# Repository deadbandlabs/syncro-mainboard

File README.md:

# Deadband Labs Syncro

|||
| :---: | :---: |
|  |  |

A USB HID force-feedback interceptor between a PC and FFB devices, based on the
MYIR MYC-YF135 SOM (STM32MP135) and fully USB bus powered.

The board has three USB-A downstream ports, with a runtime-switched two-position topology mux:

- Mode 1 (default): the PC sees the SOM as a USB gadget; downstream
  ports sit behind the hub on the SOM host port.
- Mode 2: USB-C feeds the hub uplink and downstream ports connect to the PC
  directly, with the SOM as a peer device, for downstream device management.

The board also serves as an STM32MP13 development board, with Qwiic and
mikroBUS (unpopulated) as GPIO expansion, SWD, UART debug header, user buttons
and RGB status and accent LEDs.

## Hardware

- STM32MP13, 1GHz Cortex A7, 256MB DDR3L; boots from on-module 256MB SPI NAND,
  USB DFU on SW2, or SDMMC
- USB-C device port (fixed 5.1 kOhm Rd both CC pins, no PD or CC sensing)
- FE1.1s 4-port hub, three downstream ports on horizontal USB-A, each with
  common-mode filter + ESD (ECMF02-2AMX6)
- Input eFuse (647 mA) + reverse blocking on the 5 V rail
- microSD slot (SDMMC1), console UART on a 1x3 0.1" header, SWD on a
  1.27 mm 10-pin
- Qwiic (J9), mikroBUS/Click footprint (J8), reset/DFU/case-user buttons,
  RGB status LED on TIM1, three accent RGB LEDs on TIM8 (D16-D18)
- 4 layer, 1.6 mm, ENIG, JLC04161H-3313; single-sided SMT assembly

## Opening the design

Designed in KiCad 10. Open `syncro-mainboard/syncro-mainboard.kicad_pro` from a
clone of this repository. Libraries use paths relative to the project
(`${KIPRJMOD}/../syncro-pcb-lib/`), so no library setup is needed. Vendor
datasheets, vendor 3D models, fabrication outputs and internal DFT tools are not
included. _As a result, missing-3D-model warnings are expected._ This does not affect
the schematic, layout, DRC or plots.

Part numbers as assembled are in the LCSC fields on the schematic symbols.

## Interfaces

### Qwiic (J9)

JST SH 1.0 mm, 4 pin, horizontal: `GND`, `3V3`, `SDA` (`PF3`) and `SCL` (`PH13`),
both on I2C5 and shared with the mikroBUS socket, with 10 kOhm pull-ups fitted.
Qwiic modules usually also provide pull-ups, so a long chain may over-pull the bus.
Prefer a module without pull-ups or drop bus speed to 100 kHz.

### mikroBUS / Click (J8, DNP)

Standard mikroBUS pinout on two 1x8 sockets at 22.86 mm row spacing. All 12
IO signals route to SOM GPIO, chosen for the roles below:

| Pin | mikroBUS | Board net | SOM pad | SOM port | Roles |
|---:|---|---|---:|---|---|
| 1 | `AN` | `AIO1` | 48 | PA1 | ADC1/2_INP3, TIM2_CH2, TIM5_CH2, TIM15_CH1N |
| 2 | `RST` | `RST` | 92 | PA5 | ADC1_INP2, TIM2_CH1 |
| 3 | `CS` | `SPI_CS` | 80 | PA4 | SPI1, ADC1_INP14, ClickID 1-Wire |
| 4 | `SCK` | `SPI_SCK` | 79 | PC3 | SPI1, I2S1_CK, ADC1_INP13 |
| 5 | `MISO` | `SPI_MISO` | 77 | PA6 | SPI1, ADC1_INP17, TIM3_CH1, TIM13_CH1 |
| 6 | `MOSI` | `SPI_MOSI` | 78 | PA3 | SPI1, I2S1_SDO, ADC1_INP12 |
| 7 | `3V3` | `3V3` | 16 | - | keep under 100 mA, no limit |
| 8 | `GND` | `GND` | - | - | |
| 9 | `PWM` | `AIO0` | 47 | PA2 | ADC1/2_INP1, TIM2_CH3, TIM5_CH3, TIM15_CH1 |
| 10 | `INT` | `INT` | 91 | PF11 | ADC1/2_INP8 |
| 11 | `RX` | `CAN_RX` | 96 | PB5 | FDCAN2, UART5_RX, TIM3_CH2 |
| 12 | `TX` | `CAN_TX` | 95 | PB13 | FDCAN2, UART5_TX, LPTIM2_OUT |
| 13 | `SCL` | `I2C_SCL` | 133 | PH13 | I2C5 |
| 14 | `SDA` | `I2C_SDA` | 132 | PF3 | I2C5 |
| 15 | `5V` | `SYS_5V` | - | - | board 5 V rail |
| 16 | `GND` | `GND` | - | - | |

`AN` and `PWM` use a 330 Ohm series resistor, remaining GPIO 33 Ohm
for protection. All pins share two 0.3 pF ESD arrays. `RX`/`TX`
for UART5 also support FDCAN2 directly, so a CAN transceiver Click should work.

### Console (J2) and SWD (J3)

| J2 pin | Signal |
|---:|---|
| 1 | `GND` |
| 2 | `UART4_TX` |
| 3 | `UART4_RX` |

J3 is a standard ARM Cortex Debug 10-pin, 1.27 mm: pin 1 `VTref` on `VDD_3V3`,
SWDIO/SWCLK plus reset.

### USB

- J1 (USB-C): device port; reaches the SOM in mode 1, hub port 1 in mode 2.
- J5-J7 (USB-A): hub ports 2-4, shells to GND, sharing a VBUS current limit of
  about 250 mA (200-300 mA over tolerance) set by a TPS25200.

### microSD (J4)

SDMMC1 via an EMIF06-MSD02N16, which provides series resistance, filter
capacitance, ESD and card detect on SOM pad 110 (`PD12`). Normally empty, meant
for development or as an alternate boot target using a cut trace on the bottom
of the board.

### Power budget

USB-A's ~250 mA limit leaves about 400 mA for the SOM (measured 128 mA average,
~160 mA peak), the hub (30-80 mA) and everything else, inside the 647 mA nominal
input eFuse limit (590-710 mA over tolerance, 150 kOhm ILIM). A PC USB 2.0 port
generally only guarantees 500 mA, so downstream devices should be self-powered
for best reliability.

GPIO peripherals are powered from the SOM's 3V3 output, shared with the rest of
the board and with no limiting eFuse on these pins. Keep the total under 100 mA
to avoid brownout.

## Software

The board's OS (TF-A, OP-TEE, U-Boot, Linux kernel and rootfs) is built
with the Deadband Labs Buildroot SDK:
<https://github.com/deadbandlabs/dbl-buildroot>. It builds a complete image from
upstream sources that boots the MYIR SOM, with console, USB gadget and host,
SPI NAND and SD card enabled in the device tree.

dbl-buildroot is designed to be extended by a parent project: a device tree
include applied on top of the base tree, plus a `BR2_EXTERNAL` tree adding
packages, overlays and defconfigs, see its
[Parent Integration](https://github.com/deadbandlabs/dbl-buildroot/wiki/7.-Parent-Integration)
page. Carrier board peripherals (USB hub control, Qwiic and I2C, mikroBUS and so
on) are implemented this way. The Syncro userspace and its board layer are
pending final publication and will be linked here when complete.

## Licence

Design files: CERN-OHL-W-2.0, see `LICENSE` and `NOTICE`.

A design using the board only through its external interfaces (USB ports, Qwiic,
mikroBUS/Click, console serial header and SWD) is External Material under
section 1.8 of the licence and does not need to be released. Modified design
files must be published under the same licence.

`syncro-pcb-lib/` is generated from the project's parts library (see
`syncro-pcb-lib/GENERATED.md`), and part of it derives from stock KiCad libraries,
which stay CC-BY-SA-4.0 with the KiCad libraries exception. See `NOTICE`.

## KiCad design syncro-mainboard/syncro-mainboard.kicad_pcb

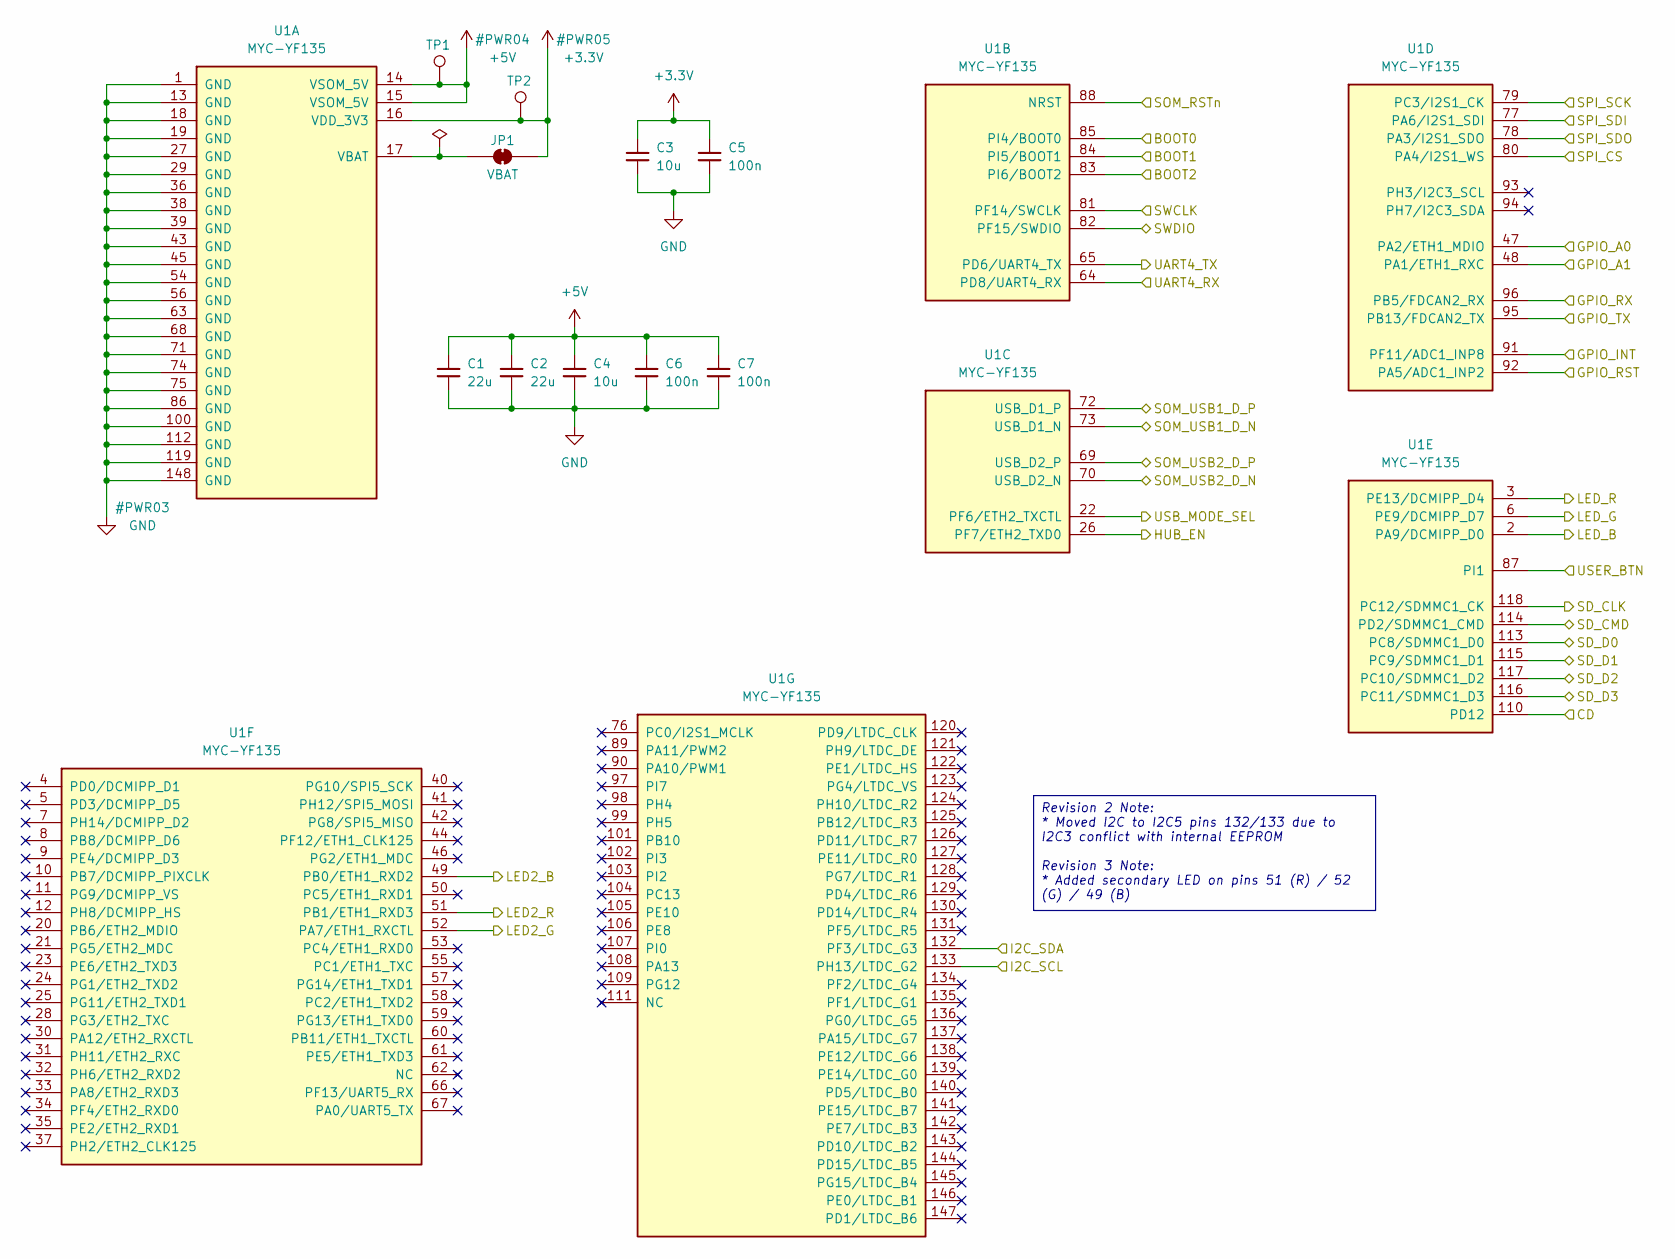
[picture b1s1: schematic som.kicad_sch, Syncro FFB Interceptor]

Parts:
C1, C2: 22u; C_0805_2012Metric; LCSC C45783
C3, C4: 10u; C_0805_2012Metric; LCSC C15850
C5, C6, C7: 100n; C_0402_1005Metric; LCSC C1525
JP1: VBAT; SolderJumper-2_P1.3mm_Bridged_RoundedPad1.0x1.5mm
TP1: 5V; TestPoint_Pad_D1.5mm
TP2: 3V3; TestPoint_Pad_D1.5mm
U1: MYC-YF135; MPN MYC-YF135F-256N256D-100-I

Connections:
+3.3V: C3.1, C5.1, JP1.2 (B), TP2.1 (1_1), U1.16 (VDD_3V3); also elsewhere on the board
+5V: C1.1, C2.1, C4.1, C6.1, C7.1, TP1.1 (1_1), U1.14 (VSOM_5V), U1.15 (VSOM_5V); also elsewhere on the board
/Debug/BOOT0: U1.85 (PI4/BOOT0); also elsewhere on the board
/Debug/BOOT1: U1.84 (PI5/BOOT1); also elsewhere on the board
/Debug/BOOT2: U1.83 (PI6/BOOT2); also elsewhere on the board
/Debug/SOM_RSTn: U1.88 (NRST); also elsewhere on the board
/Debug/SWCLK: U1.81 (PF14/SWCLK); also elsewhere on the board
/Debug/SWDIO: U1.82 (PF15/SWDIO); also elsewhere on the board
/Debug/UART4_RX: U1.64 (PD8/UART4_RX); also elsewhere on the board
/Debug/UART4_TX: U1.65 (PD6/UART4_TX); also elsewhere on the board
/STM32MP13 SOM/GPIO_A0: U1.47 (PA2/ETH1_MDIO); also elsewhere on the board
/STM32MP13 SOM/GPIO_A1: U1.48 (PA1/ETH1_RXC); also elsewhere on the board
/STM32MP13 SOM/GPIO_INT: U1.91 (PF11/ADC1_INP8); also elsewhere on the board
/STM32MP13 SOM/GPIO_RST: U1.92 (PA5/ADC1_INP2); also elsewhere on the board
/STM32MP13 SOM/GPIO_RX: U1.96 (PB5/FDCAN2_RX); also elsewhere on the board
/STM32MP13 SOM/GPIO_TX: U1.95 (PB13/FDCAN2_TX); also elsewhere on the board
/STM32MP13 SOM/HUB_EN: U1.26 (PF7/ETH2_TXD0); also elsewhere on the board
/STM32MP13 SOM/I2C_SCL: U1.133 (PH13/LTDC_G2); also elsewhere on the board
/STM32MP13 SOM/I2C_SDA: U1.132 (PF3/LTDC_G3); also elsewhere on the board
/STM32MP13 SOM/LED2_B: U1.49 (PB0/ETH1_RXD2); also elsewhere on the board
/STM32MP13 SOM/LED2_G: U1.52 (PA7/ETH1_RXCTL); also elsewhere on the board
/STM32MP13 SOM/LED2_R: U1.51 (PB1/ETH1_RXD3); also elsewhere on the board
/STM32MP13 SOM/LED_B: U1.2 (PA9/DCMIPP_D0); also elsewhere on the board
/STM32MP13 SOM/LED_G: U1.6 (PE9/DCMIPP_D7); also elsewhere on the board
/STM32MP13 SOM/LED_R: U1.3 (PE13/DCMIPP_D4); also elsewhere on the board
/STM32MP13 SOM/SD_CLK: U1.118 (PC12/SDMMC1_CK); also elsewhere on the board
/STM32MP13 SOM/SD_CMD: U1.114 (PD2/SDMMC1_CMD); also elsewhere on the board
/STM32MP13 SOM/SD_D0: U1.113 (PC8/SDMMC1_D0); also elsewhere on the board
/STM32MP13 SOM/SD_D1: U1.115 (PC9/SDMMC1_D1); also elsewhere on the board
/STM32MP13 SOM/SD_D2: U1.117 (PC10/SDMMC1_D2); also elsewhere on the board
/STM32MP13 SOM/SD_D3: U1.116 (PC11/SDMMC1_D3); also elsewhere on the board
/STM32MP13 SOM/SOM_USB1_D_N: U1.73 (USB_D1_N); also elsewhere on the board
/STM32MP13 SOM/SOM_USB1_D_P: U1.72 (USB_D1_P); also elsewhere on the board
/STM32MP13 SOM/SOM_USB2_D_N: U1.70 (USB_D2_N); also elsewhere on the board
/STM32MP13 SOM/SOM_USB2_D_P: U1.69 (USB_D2_P); also elsewhere on the board
/STM32MP13 SOM/SPI_CS: U1.80 (PA4/I2S1_WS); also elsewhere on the board
/STM32MP13 SOM/SPI_SCK: U1.79 (PC3/I2S1_CK); also elsewhere on the board
/STM32MP13 SOM/SPI_SDI: U1.77 (PA6/I2S1_SDI); also elsewhere on the board
/STM32MP13 SOM/SPI_SDO: U1.78 (PA3/I2S1_SDO); also elsewhere on the board
/STM32MP13 SOM/USB_MODE_SEL: U1.22 (PF6/ETH2_TXCTL); also elsewhere on the board
/STM32MP13 SOM/USER_BTN: U1.87 (PI1); also elsewhere on the board
/System IO/CD: U1.110 (PD12); also elsewhere on the board
GND: C1.2, C2.2, C3.2, C4.2, C5.2, C6.2, C7.2, U1.1 (GND), U1.13 (GND), U1.18 (GND), U1.19 (GND), U1.27 (GND), U1.29 (GND), U1.36 (GND), U1.38 (GND), U1.39 (GND), U1.43 (GND), U1.45 (GND), U1.54 (GND), U1.56 (GND), U1.63 (GND), U1.68 (GND), U1.71 (GND), U1.74 (GND), U1.75 (GND), U1.86 (GND), U1.100 (GND), U1.112 (GND), U1.119 (GND), U1.148 (GND); also elsewhere on the board
unnamed: JP1.1 (A), U1.17 (VBAT)

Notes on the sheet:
Revision 2 Note: * Moved I2C to I2C5 pins 132/133 due to I2C3 conflict with internal EEPROM Revision 3 Note: * Added secondary LED on pins 51 (R) / 52 (G) / 49 (B)

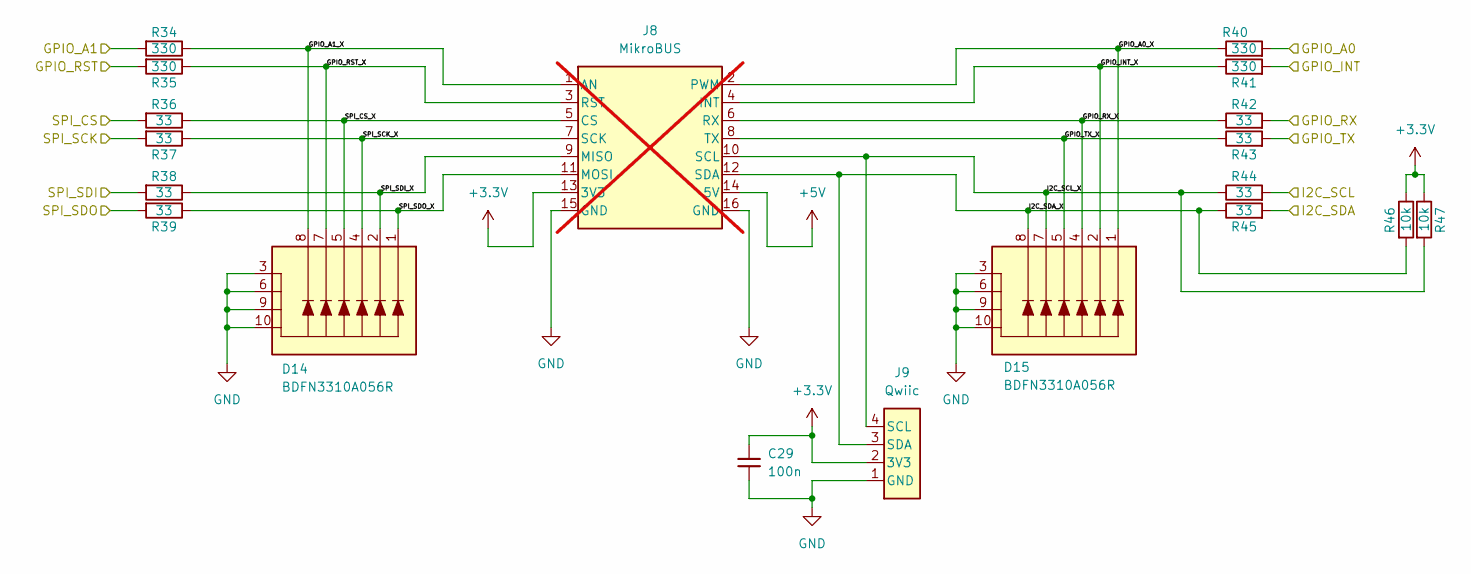
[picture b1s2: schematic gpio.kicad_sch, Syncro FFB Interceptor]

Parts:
C29: 100n; C_0402_1005Metric; LCSC C1525
D14, D15: BDFN3310A056R; BDFN3310-10_3.3x1.0mm_P0.4mm; LCSC C600810
J8: MikroBUS; MikroBUS_Socket_2x1x08_P2.54mm; not fitted
J9: Qwiic; JST_SH_SM04B-SRSS-TB_1x04-1MP_P1.00mm_Horizontal; LCSC C2905006
R34, R35, R40, R41: 330; R_0402_1005Metric; LCSC C25104
R36, R37, R38, R39, R42, R43, R44, R45: 33; R_0402_1005Metric; LCSC C25105
R46, R47: 10k; R_0402_1005Metric; LCSC C25744

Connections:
+3.3V: C29.1, J8.13 (3V3), J9.2 (3V3), R46.1, R47.1; also elsewhere on the board
+5V: J8.14 (5V); also elsewhere on the board
/STM32MP13 SOM/GPIO_A0: R40.2; also elsewhere on the board
/STM32MP13 SOM/GPIO_A1: R34.2; also elsewhere on the board
/STM32MP13 SOM/GPIO_INT: R41.2; also elsewhere on the board
/STM32MP13 SOM/GPIO_RST: R35.2; also elsewhere on the board
/STM32MP13 SOM/GPIO_RX: R42.2; also elsewhere on the board
/STM32MP13 SOM/GPIO_TX: R43.2; also elsewhere on the board
/STM32MP13 SOM/I2C_SCL: R44.2; also elsewhere on the board
/STM32MP13 SOM/I2C_SDA: R45.2; also elsewhere on the board
/STM32MP13 SOM/SPI_CS: R36.2; also elsewhere on the board
/STM32MP13 SOM/SPI_SCK: R37.2; also elsewhere on the board
/STM32MP13 SOM/SPI_SDI: R38.2; also elsewhere on the board
/STM32MP13 SOM/SPI_SDO: R39.2; also elsewhere on the board
/User GPIO/GPIO_A0_X: D15.1 (IO1), J8.2 (PWM), R40.1
/User GPIO/GPIO_A1_X: D14.8 (IO6), J8.1 (AN), R34.1
/User GPIO/GPIO_INT_X: D15.2 (IO2), J8.4 (INT), R41.1
/User GPIO/GPIO_RST_X: D14.7 (IO5), J8.3 (RST), R35.1
/User GPIO/GPIO_RX_X: D15.4 (IO3), J8.6 (RX), R42.1
/User GPIO/GPIO_TX_X: D15.5 (IO4), J8.8 (TX), R43.1
/User GPIO/I2C_SCL_X: D15.7 (IO5), J8.10 (SCL), J9.4 (SCL), R44.1, R47.2
/User GPIO/I2C_SDA_X: D15.8 (IO6), J8.12 (SDA), J9.3 (SDA), R45.1, R46.2
/User GPIO/SPI_CS_X: D14.5 (IO4), J8.5 (CS), R36.1
/User GPIO/SPI_SCK_X: D14.4 (IO3), J8.7 (SCK), R37.1
/User GPIO/SPI_SDI_X: D14.2 (IO2), J8.9 (MISO), R38.1
/User GPIO/SPI_SDO_X: D14.1 (IO1), J8.11 (MOSI), R39.1
GND: C29.2, D14.3 (GND), D14.6 (GND), D14.9 (GND), D14.10 (GND), D15.3 (GND), D15.6 (GND), D15.9 (GND), D15.10 (GND), J8.15 (GND), J8.16 (GND), J9.1 (GND); also elsewhere on the board

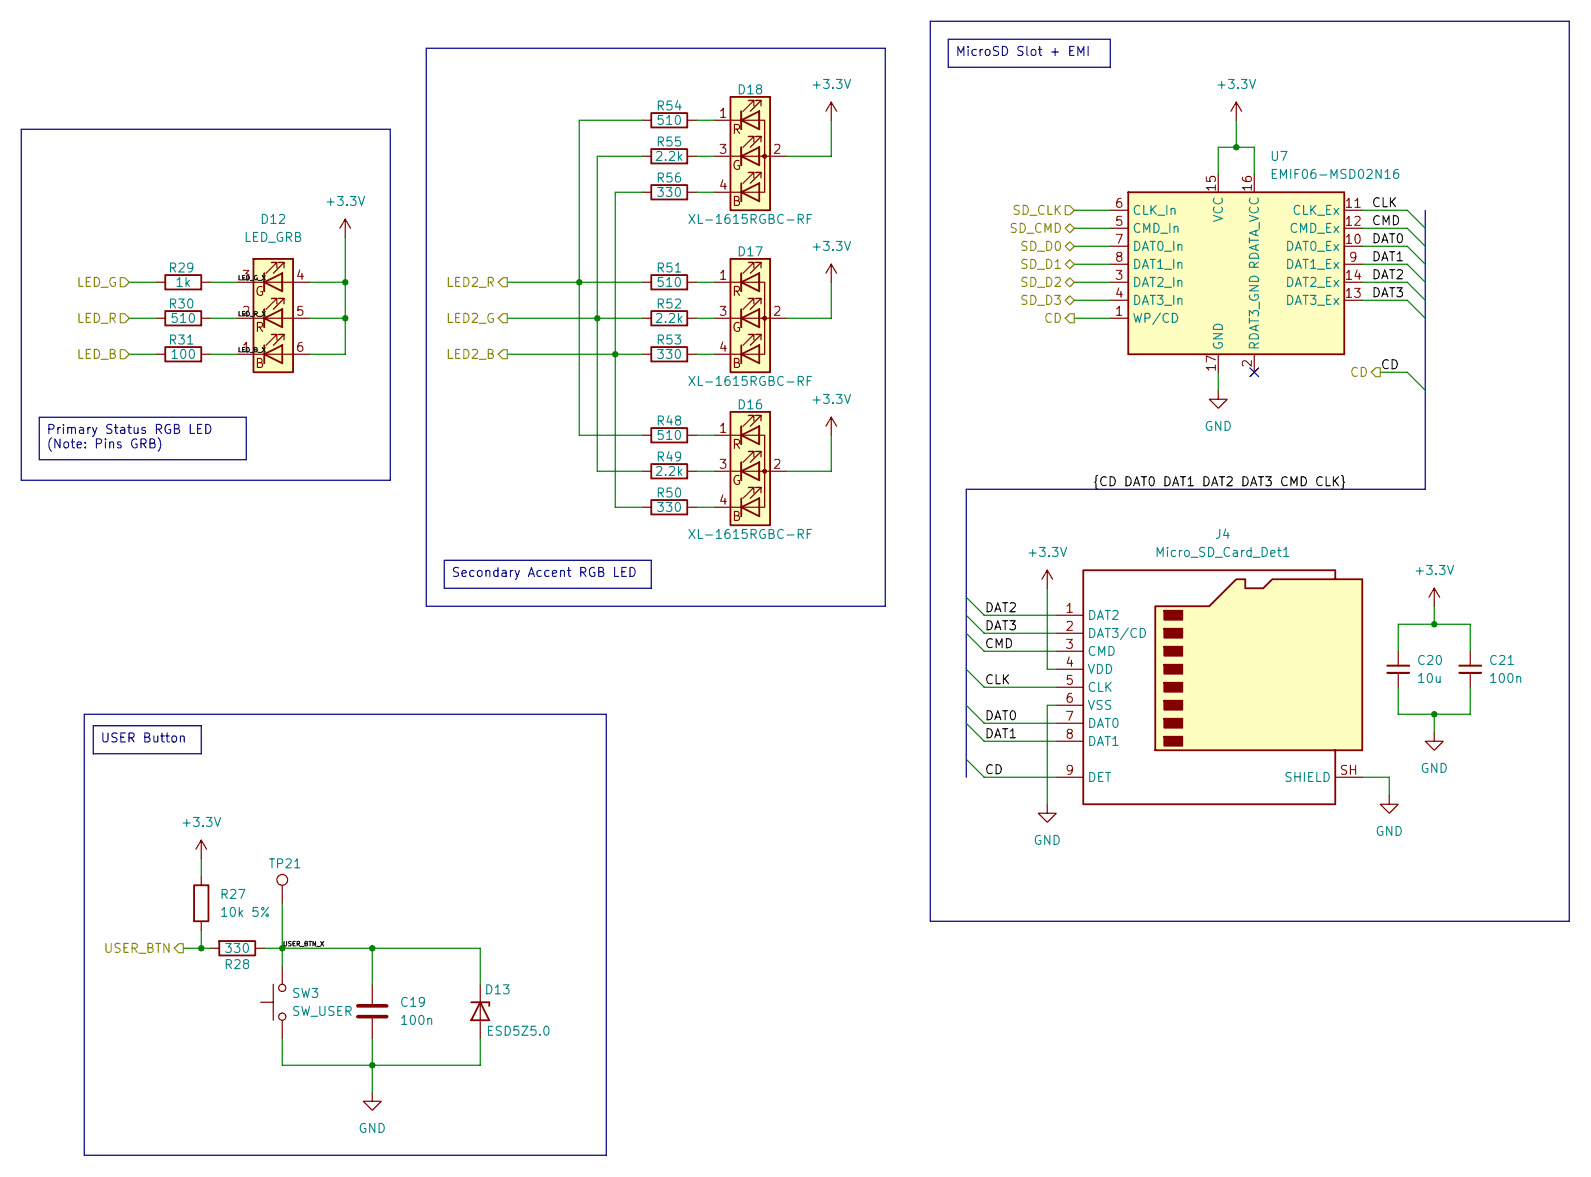
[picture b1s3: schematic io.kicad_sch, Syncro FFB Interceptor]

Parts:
C19, C21: 100n; C_0402_1005Metric; LCSC C1525
C20: 10u; C_0805_2012Metric; LCSC C15850
D12: LED_GRB; LED_RGB_5050-6; MPN TJ-S5050UG2W5TLCBRG-A5; LCSC C440459
D13: ESD5Z5.0; D_SOD-523; LCSC C3008120
D16, D17, D18: XL-1615RGBC-RF; LED_RGB_XINGLIGHT_XL-1615RGBC; MPN XL-1615RGBC-RF; LCSC C965840
J4: Micro_SD_Card_Det1; microSD_SHOUHAN_TF-CARD-H1.8-SY; MPN TF-CARD H1.8 SY; LCSC C7529391
R27: 10k 5%; R_0402_1005Metric; LCSC C25744
R28, R50, R53, R56: 330; R_0402_1005Metric; LCSC C25104
R29: 1k; R_0402_1005Metric; LCSC C11702
R30, R48, R51, R54: 510; R_0402_1005Metric; LCSC C25123
R31: 100; R_0402_1005Metric; LCSC C25076
R49, R52, R55: 2.2k; R_0402_1005Metric; LCSC C25879
SW3: SW_USER; SW_Push_1P1T_NO_E-Switch_TL3301NxxxxxG; LCSC C111608
TP21: BTN; TestPoint_Pad_D1.5mm
U7: EMIF06-MSD02N16; EMIF06-MSD02N16_uQFN-16_3.5x1.2mm_P0.4mm; MPN EMIF06-MSD02N16; LCSC C5267594

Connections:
+3.3V: C20.1, C21.1, D12.4 (GA), D12.5 (RA), D12.6 (BA), D16.2 (A), D17.2 (A), D18.2 (A), J4.4 (VDD), R27.1, U7.15 (VCC), U7.16 (RDATA_VCC); also elsewhere on the board
/STM32MP13 SOM/LED2_B: R50.1, R53.1, R56.1; also elsewhere on the board
/STM32MP13 SOM/LED2_G: R49.1, R52.1, R55.1; also elsewhere on the board
/STM32MP13 SOM/LED2_R: R48.1, R51.1, R54.1; also elsewhere on the board
/STM32MP13 SOM/LED_B: R31.1; also elsewhere on the board
/STM32MP13 SOM/LED_G: R29.1; also elsewhere on the board
/STM32MP13 SOM/LED_R: R30.1; also elsewhere on the board
/STM32MP13 SOM/SD_CLK: U7.6 (CLK_In); also elsewhere on the board
/STM32MP13 SOM/SD_CMD: U7.5 (CMD_In); also elsewhere on the board
/STM32MP13 SOM/SD_D0: U7.7 (DAT0_In); also elsewhere on the board
/STM32MP13 SOM/SD_D1: U7.8 (DAT1_In); also elsewhere on the board
/STM32MP13 SOM/SD_D2: U7.3 (DAT2_In); also elsewhere on the board
/STM32MP13 SOM/SD_D3: U7.4 (DAT3_In); also elsewhere on the board
/STM32MP13 SOM/USER_BTN: R27.2, R28.2; also elsewhere on the board
/System IO/CD: J4.9 (DET), U7.1 (WP/CD); also elsewhere on the board
/System IO/CLK: J4.5 (CLK), U7.11 (CLK_Ex)
/System IO/CMD: J4.3 (CMD), U7.12 (CMD_Ex)
/System IO/DAT0: J4.7 (DAT0), U7.10 (DAT0_Ex)
/System IO/DAT1: J4.8 (DAT1), U7.9 (DAT1_Ex)
/System IO/DAT2: J4.1 (DAT2), U7.14 (DAT2_Ex)
/System IO/DAT3: J4.2 (DAT3/CD), U7.13 (DAT3_Ex)
/System IO/LED_B_X: D12.1 (BK), R31.2
/System IO/LED_G_X: D12.3 (GK), R29.2
/System IO/LED_R_X: D12.2 (RK), R30.2
/System IO/USER_BTN_X: C19.1, D13.1 (K), R28.1, SW3.2, TP21.1 (1_1)
GND: C19.2, C20.2, C21.2, D13.2 (A), J4.6 (VSS), J4.SH (SHIELD), SW3.1, U7.17 (GND); also elsewhere on the board
unnamed: D16.4 (BK), R50.2
unnamed: D16.3 (GK), R49.2
unnamed: D16.1 (RK), R48.2
unnamed: D17.4 (BK), R53.2
unnamed: D17.3 (GK), R52.2
unnamed: D17.1 (RK), R51.2
unnamed: D18.4 (BK), R56.2
unnamed: D18.3 (GK), R55.2
unnamed: D18.1 (RK), R54.2

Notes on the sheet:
MicroSD Slot + EMI
Secondary Accent RGB LED
Primary Status RGB LED (Note: Pins GRB)
USER Button

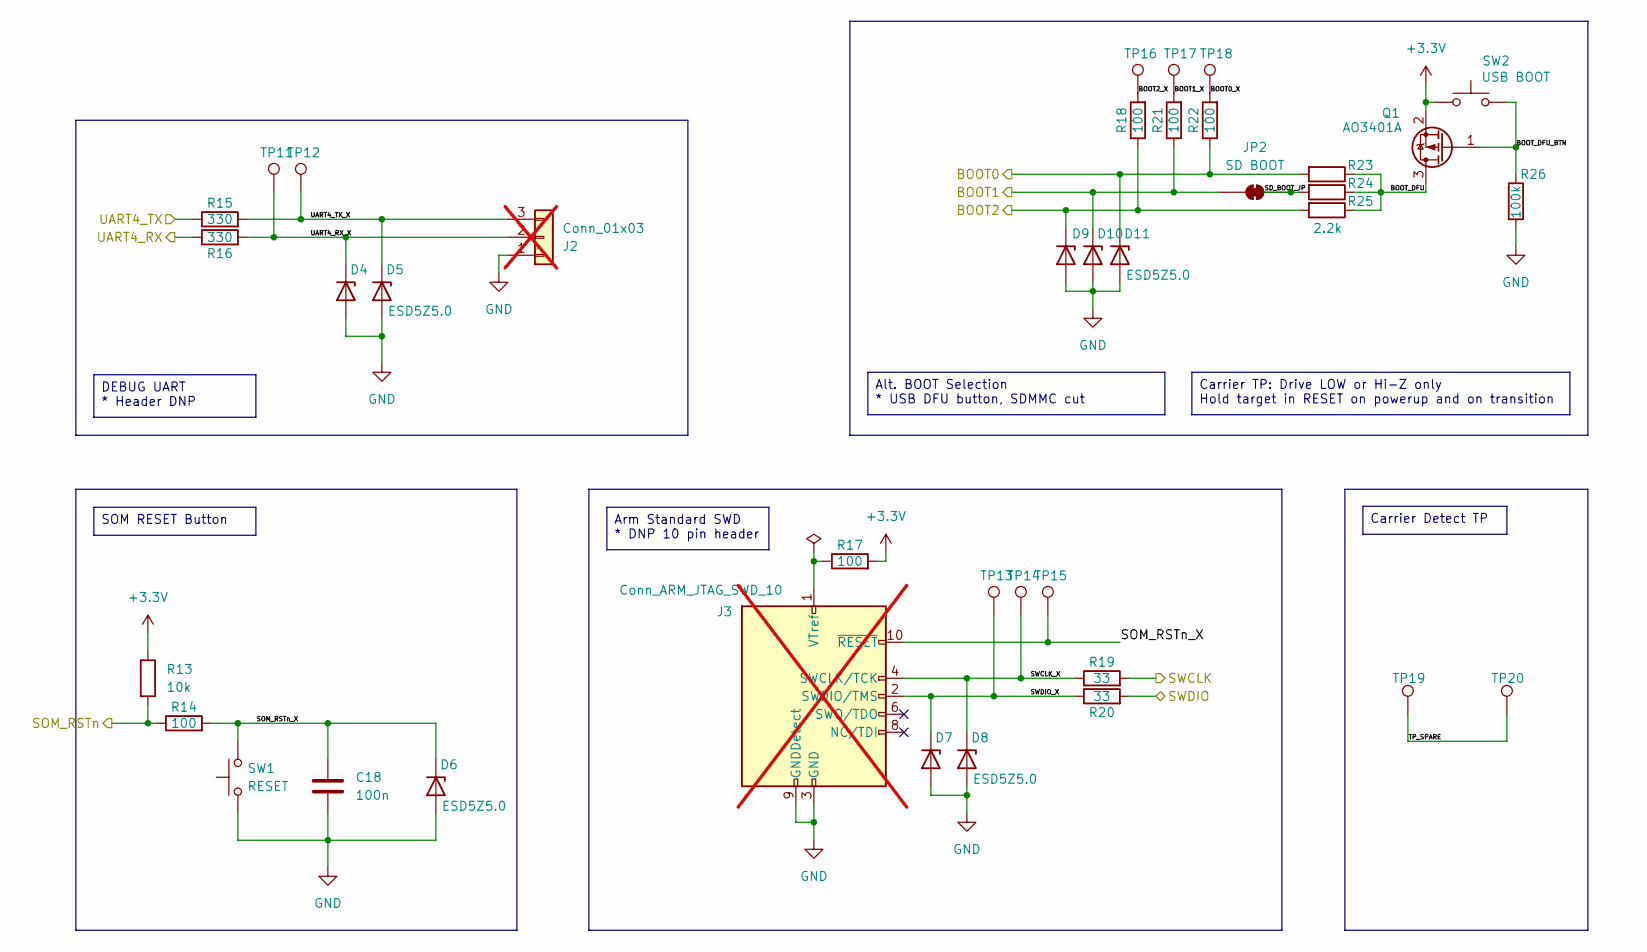
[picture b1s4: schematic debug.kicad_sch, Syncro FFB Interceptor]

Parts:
C18: 100n; C_0402_1005Metric; LCSC C1525
D4, D5, D6, D7, D8, D9, D10, D11: ESD5Z5.0; D_SOD-523; LCSC C3008120
J2: Conn_01x03; PinHeader_1x03_P2.54mm_Vertical; not fitted
J3: Conn_ARM_JTAG_SWD_10; PinSocket_2x05_P1.27mm_Vertical_SMD; not fitted
JP2: SD BOOT; SolderJumper-2_P1.3mm_Bridged_RoundedPad1.0x1.5mm
Q1: AO3401A; SOT-23; LCSC C15127
R13: 10k; R_0402_1005Metric; LCSC C25744
R14, R17, R18, R21, R22: 100; R_0402_1005Metric; LCSC C25076
R15, R16: 330; R_0402_1005Metric; LCSC C25104
R19, R20: 33; R_0402_1005Metric; LCSC C25105
R23, R24, R25: 2.2k; R_0402_1005Metric; LCSC C25879
R26: 100k; R_0402_1005Metric; LCSC C25741
SW1: RESET; SW_Push_1P1T_XKB_TS-1187A; LCSC C318884
SW2: USB BOOT; SW_Push_1P1T_XKB_TS-1187A; LCSC C318884
TP11: RX; TestPoint_Pad_D1.5mm
TP12: TX; TestPoint_Pad_D1.5mm
TP13: SWCLK; TestPoint_Pad_D1.5mm
TP14: SWDIO; TestPoint_Pad_D1.5mm
TP15: RST; TestPoint_Pad_D1.5mm
TP16: BOOT2; TestPoint_Pad_D1.5mm
TP17: BOOT1; TestPoint_Pad_D1.5mm
TP18: BOOT0; TestPoint_Pad_D1.5mm
TP19: BRD_A; TestPoint_Pad_D1.5mm
TP20: BRD_B; TestPoint_Pad_D1.5mm

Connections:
+3.3V: Q1.2 (S), R13.1, R17.2, SW2.1; also elsewhere on the board
/Debug/BOOT0: D11.1 (K), R22.1, R23.2; also elsewhere on the board
/Debug/BOOT0_X: R22.2, TP18.1 (1_1)
/Debug/BOOT1: D10.1 (K), JP2.1 (A), R21.1; also elsewhere on the board
/Debug/BOOT1_X: R21.2, TP17.1 (1_1)
/Debug/BOOT2: D9.1 (K), R18.1, R25.2; also elsewhere on the board
/Debug/BOOT2_X: R18.2, TP16.1 (1_1)
/Debug/BOOT_DFU: Q1.3 (D), R23.1, R24.1, R25.1
/Debug/BOOT_DFU_BTN: Q1.1 (G), R26.1, SW2.2
/Debug/SD_BOOT_JP: JP2.2 (B), R24.2
/Debug/SOM_RSTn: R13.2, R14.1; also elsewhere on the board
/Debug/SOM_RSTn_X: C18.1, D6.1 (K), J3.10 (~RESET), R14.2, SW1.2, TP15.1 (1_1)
/Debug/SWCLK: R19.2; also elsewhere on the board
/Debug/SWCLK_X: D8.1 (K), J3.4 (SWCLK/TCK), R19.1, TP14.1 (1_1)
/Debug/SWDIO: R20.2; also elsewhere on the board
/Debug/SWDIO_X: D7.1 (K), J3.2 (SWDIO/TMS), R20.1, TP13.1 (1_1)
/Debug/TP_SPARE: TP19.1 (1_1), TP20.1 (1_1)
/Debug/UART4_RX: R16.1; also elsewhere on the board
/Debug/UART4_RX_X: D4.1 (K), J2.2, R16.2, TP11.1 (1_1)
/Debug/UART4_TX: R15.1; also elsewhere on the board
/Debug/UART4_TX_X: D5.1 (K), J2.3, R15.2, TP12.1 (1_1)
GND: C18.2, D4.2 (A), D5.2 (A), D6.2 (A), D7.2 (A), D8.2 (A), D9.2 (A), D10.2 (A), D11.2 (A), J2.1, J3.3 (GND), J3.5 (GND), J3.9 (GNDDetect), R26.2, SW1.1; also elsewhere on the board
unnamed: J3.1 (VTref), R17.1

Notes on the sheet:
Arm Standard SWD * DNP 10 pin header
Carrier TP: Drive LOW or Hi-Z only Hold target in RESET on powerup and on transition
Alt. BOOT Selection * USB DFU button, SDMMC cut
Carrier Detect TP
SOM RESET Button
DEBUG UART * Header DNP

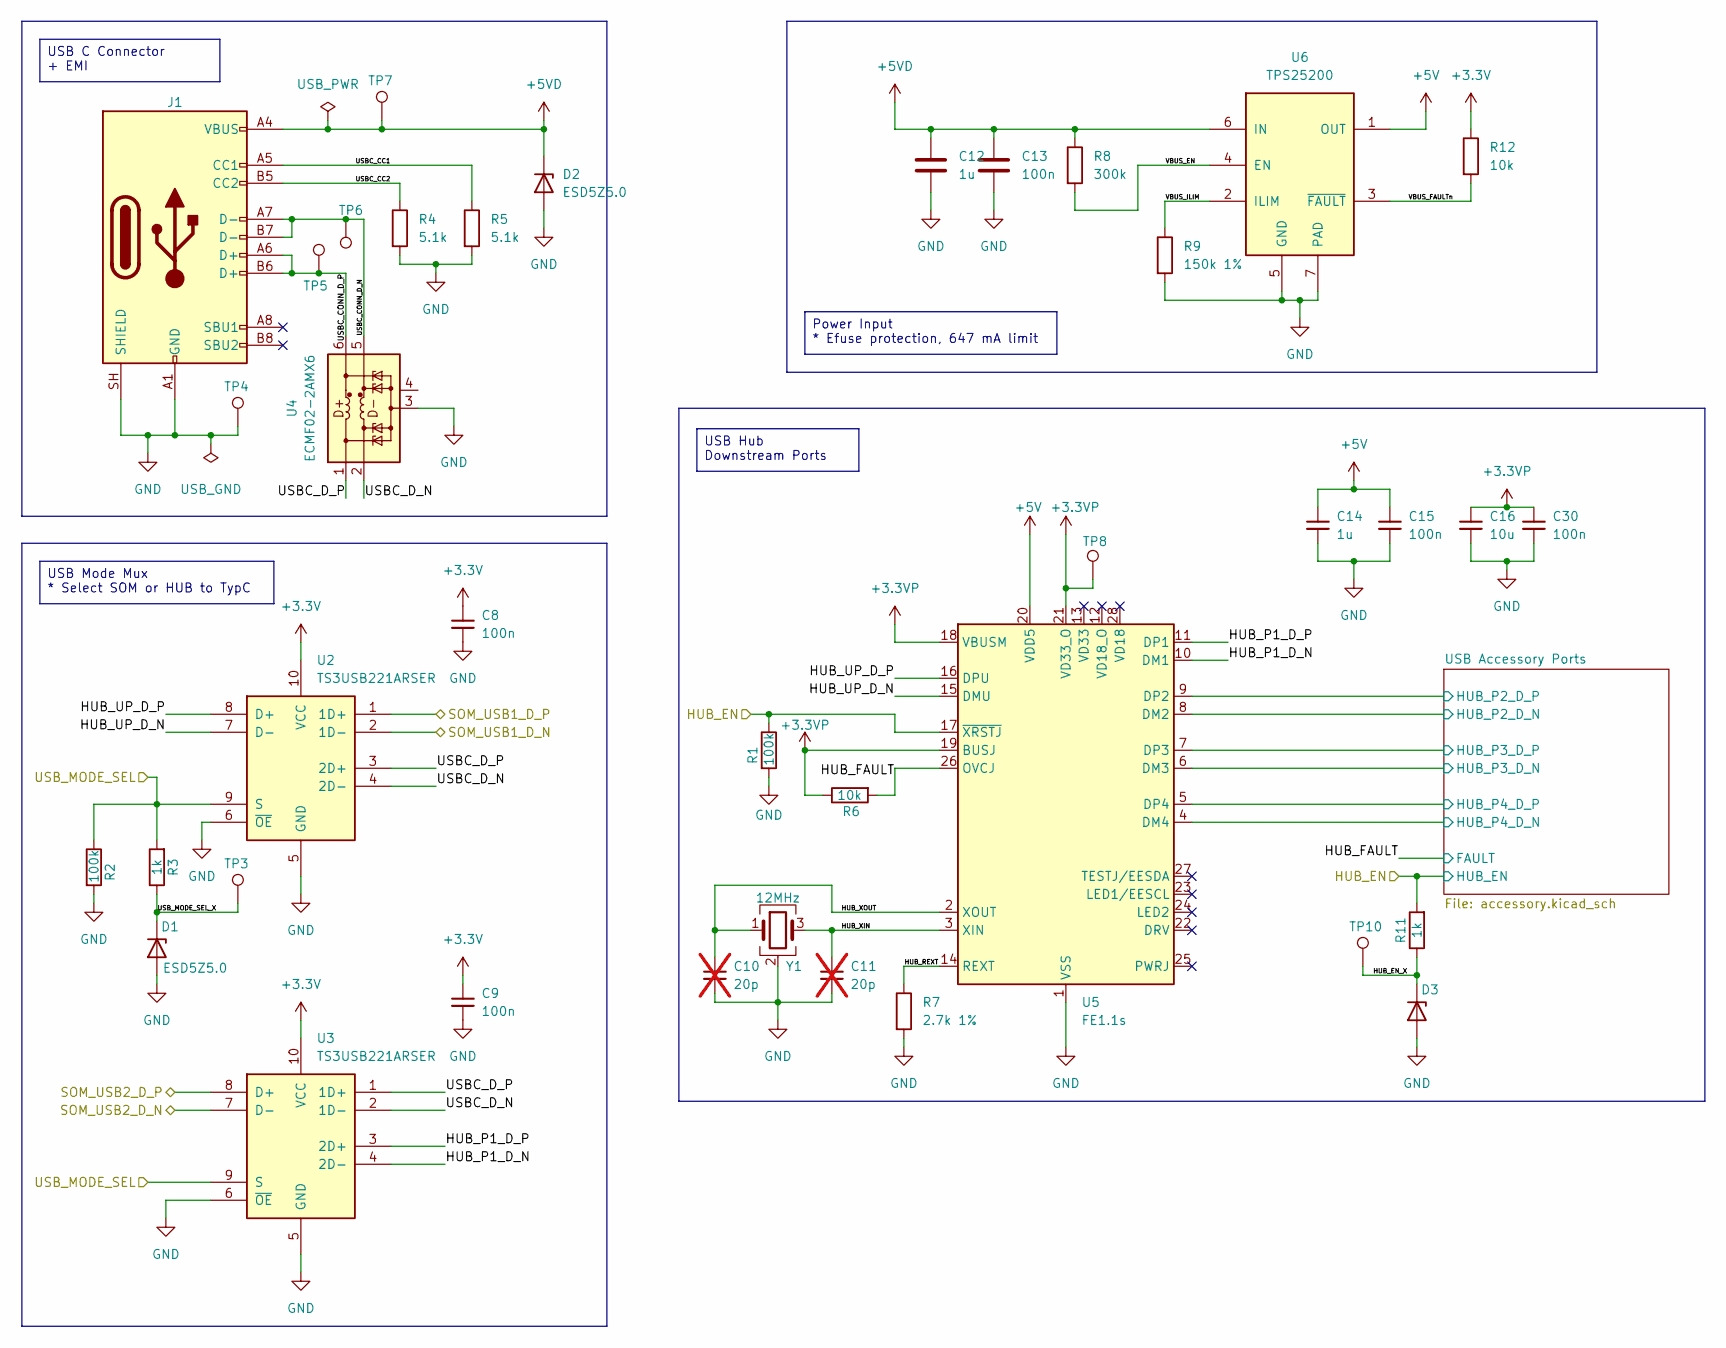
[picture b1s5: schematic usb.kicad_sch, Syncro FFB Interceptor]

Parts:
C8, C9, C13, C15, C30: 100n; C_0402_1005Metric; LCSC C1525
C10, C11: 20p; C_0402_1005Metric; MPN 0402CG200J500NT; LCSC C1554; not fitted
C12, C14: 1u; C_0402_1005Metric; LCSC C52923
C16: 10u; C_0805_2012Metric; LCSC C15850
D1, D2, D3: ESD5Z5.0; D_SOD-523; LCSC C3008120
J1: USB_C_Receptacle_USB2.0_16P; USB_C_Receptacle_SHOUHAN_TYPE-C-16PIN-2MD-073; MPN TYPE-C-16PIN-2MD-073; LCSC C2765186
R1, R2: 100k; R_0402_1005Metric; LCSC C25741
R3, R11: 1k; R_0402_1005Metric; LCSC C11702
R4, R5: 5.1k; R_0402_1005Metric; LCSC C25905
R6, R12: 10k; R_0402_1005Metric; LCSC C25744
R7: 2.7k 1%; R_0402_1005Metric; LCSC C25885
R8: 300k; R_0402_1005Metric; LCSC C25774
R9: 150k 1%; R_0402_1005Metric; LCSC C25755
TP3: MODE; TestPoint_Pad_D1.5mm
TP4: GND; TestPoint_Pad_D1.5mm
TP5: DP; TestPoint_Pad_D1.5mm
TP6: DM; TestPoint_Pad_D1.5mm
TP7: VBUS; TestPoint_Pad_D1.5mm
TP8: 3V3P; TestPoint_Pad_D1.5mm
TP10: USBEN; TestPoint_Pad_D1.5mm
U2, U3: TS3USB221ARSER; Texas_UQFN-10_1.5x2mm_P0.5mm; MPN TS3USB221ARSER; LCSC C128396
U4: ECMF02-2AMX6; ST_UQFN-6L_1.5x1.7mm_P0.5mm; MPN ECMF02-2AMX6; LCSC C2651144
U5: FE1.1s; SSOP-28_3.9x9.9mm_P0.635mm; MPN FE1.1S-BSOP28BCNTR; LCSC C42383361
U6: TPS25200; WSON-6-1EP_2x2mm_P0.65mm_EP1x1.6mm_ThermalVias_0.3mm; MPN TPS25200DRVR; LCSC C128401
Y1: 12MHz; Crystal_SMD_3225-4Pin_3.2x2.5mm; MPN X322512MSB4SI; LCSC C9002

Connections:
+3.3V: C8.1, C9.1, R12.1, U2.10 (VCC), U3.10 (VCC); also elsewhere on the board
+3.3VP: C16.1, C30.1, R6.1, TP8.1 (1_1), U5.18 (VBUSM), U5.19 (BUSJ), U5.21 (VD33_O)
+5V: C14.1, C15.1, U5.20 (VDD5), U6.1 (OUT); also elsewhere on the board
+5VD: C12.1, C13.1, D2.1 (K), J1.A4 (VBUS), J1.A9 (VBUS), J1.B4 (VBUS), J1.B9 (VBUS), R8.1, TP7.1 (1_1), U6.6 (IN)
/STM32MP13 SOM/HUB_EN: R1.1, R11.2, U5.17 (~XRSTJ); also elsewhere on the board
/STM32MP13 SOM/SOM_USB1_D_N: U2.2 (1D-); also elsewhere on the board
/STM32MP13 SOM/SOM_USB1_D_P: U2.1 (1D+); also elsewhere on the board
/STM32MP13 SOM/SOM_USB2_D_N: U3.7 (D-); also elsewhere on the board
/STM32MP13 SOM/SOM_USB2_D_P: U3.8 (D+); also elsewhere on the board
/STM32MP13 SOM/USB_MODE_SEL: R2.1, R3.2, U2.9 (S), U3.9 (S); also elsewhere on the board
/USB Mux/HUB_EN_X: D3.1 (K), R11.1, TP10.1 (1_1)
/USB Mux/HUB_FAULT: R6.2, U5.26 (OVCJ); also elsewhere on the board
/USB Mux/HUB_P1_D_N: U3.4 (2D-), U5.10 (DM1)
/USB Mux/HUB_P1_D_P: U3.3 (2D+), U5.11 (DP1)
/USB Mux/HUB_REXT: R7.1, U5.14 (REXT)
/USB Mux/HUB_UP_D_N: U2.7 (D-), U5.15 (DMU)
/USB Mux/HUB_UP_D_P: U2.8 (D+), U5.16 (DPU)
/USB Mux/HUB_XIN: C11.1, U5.3 (XIN), Y1.3
/USB Mux/HUB_XOUT: C10.1, U5.2 (XOUT), Y1.1
/USB Mux/USB Accessory Ports/HUB_P2_D_N: U5.8 (DM2); also elsewhere on the board
/USB Mux/USB Accessory Ports/HUB_P2_D_P: U5.9 (DP2); also elsewhere on the board
/USB Mux/USB Accessory Ports/HUB_P3_D_N: U5.6 (DM3); also elsewhere on the board
/USB Mux/USB Accessory Ports/HUB_P3_D_P: U5.7 (DP3); also elsewhere on the board
/USB Mux/USB Accessory Ports/HUB_P4_D_N: U5.4 (DM4); also elsewhere on the board
/USB Mux/USB Accessory Ports/HUB_P4_D_P: U5.5 (DP4); also elsewhere on the board
/USB Mux/USBC_CC1: J1.A5 (CC1), R5.1
/USB Mux/USBC_CC2: J1.B5 (CC2), R4.1
/USB Mux/USBC_CONN_D_N: J1.A7 (D-), J1.B7 (D-), TP6.1 (1_1), U4.5 (D-_out)
/USB Mux/USBC_CONN_D_P: J1.A6 (D+), J1.B6 (D+), TP5.1 (1_1), U4.6 (D+_out)
/USB Mux/USBC_D_N: U2.4 (2D-), U3.2 (1D-), U4.2 (D-_in)
/USB Mux/USBC_D_P: U2.3 (2D+), U3.1 (1D+), U4.1 (D+_in)
/USB Mux/USB_MODE_SEL_X: D1.1 (K), R3.1, TP3.1 (1_1)
/USB Mux/VBUS_EN: R8.2, U6.4 (EN)
/USB Mux/VBUS_FAULTn: R12.2, U6.3 (~FAULT)
/USB Mux/VBUS_ILIM: R9.1, U6.2 (ILIM)
GND: C8.2, C9.2, C10.2, C11.2, C12.2, C13.2, C14.2, C15.2, C16.2, C30.2, D1.2 (A), D2.2 (A), D3.2 (A), J1.A1 (GND), J1.A12 (GND), J1.B1 (GND), J1.B12 (GND), J1.SH (SHIELD), R1.2, R2.2, R4.2, R5.2, R7.2, R9.2, TP4.1 (1_1), U2.5 (GND), U2.6 (~OE), U3.5 (GND), U3.6 (~OE), U4.3 (GND), U5.1 (VSS), U6.5 (GND), U6.7 (PAD), Y1.2 (G), Y1.4 (G); also elsewhere on the board

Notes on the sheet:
Power Input * Efuse protection, 647 mA limit
USB Mode Mux * Select SOM or HUB to TypC
USB Hub Downstream Ports
USB C Connector + EMI
